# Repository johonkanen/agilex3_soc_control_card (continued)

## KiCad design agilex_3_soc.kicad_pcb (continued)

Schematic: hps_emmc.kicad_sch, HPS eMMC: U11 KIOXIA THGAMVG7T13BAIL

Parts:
C242, C244: 4u7; C_0402_1005Metric; LCSC C318563
C243: 100n; C_0201_0603Metric; LCSC C190183
C245: 220n; C_0201_0603Metric; LCSC C76932
C246: 2u2; C_0201_0603Metric; LCSC C77762
R241, R242, R243, R272, R273, R274, R275, R276, R277, R278, R279: 10k; R_0201_0603Metric; LCSC C473048
R280, R281, R282, R283, R284, R285, R286, R287, R288, R289, R290: 33R; R_0201_0603Metric; LCSC C320843
U11: THGAMVG7T13BAIL; LFBGA-153_11.5x13mm_Layout14x14_P0.5mm; LCSC C7599693

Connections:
1V8: C242.1, C243.1, R241.1, R243.1, R272.1, R273.1, R274.1, R275.1, R276.1, R277.1, R278.1, R279.1, U11.C6 (VCCQ), U11.M4 (VCCQ), U11.N4 (VCCQ), U11.P3 (VCCQ), U11.P5 (VCCQ); also elsewhere on the board
3V3: C244.1, C245.1, U11.E6 (VCC), U11.F5 (VCC), U11.J10 (VCC), U11.K9 (VCC); also elsewhere on the board
/hps_emmc/emmc_ds: R242.1, R290.2, U11.H5 (DS)
/hps_emmc/emmc_ds_hps: R290.1; also elsewhere on the board
/hps_emmc/emmc_rst_n: R243.2, U11.K5 (RST_n); also elsewhere on the board
/hps_emmc/sd_clk: R280.2, U11.M6 (CLK)
/hps_emmc/sd_clk_hps: R280.1; also elsewhere on the board
/hps_emmc/sd_cmd: R241.2, R281.2, U11.M5 (CMD)
/hps_emmc/sd_cmd_hps: R281.1; also elsewhere on the board
/hps_emmc/sd_d0: R272.2, R282.2, U11.A3 (DAT0)
/hps_emmc/sd_d0_hps: R282.1; also elsewhere on the board
/hps_emmc/sd_d1: R273.2, R283.2, U11.A4 (DAT1)
/hps_emmc/sd_d1_hps: R283.1; also elsewhere on the board
/hps_emmc/sd_d2: R274.2, R284.2, U11.A5 (DAT2)
/hps_emmc/sd_d2_hps: R284.1; also elsewhere on the board
/hps_emmc/sd_d3: R275.2, R285.2, U11.B2 (DAT3)
/hps_emmc/sd_d3_hps: R285.1; also elsewhere on the board
/hps_emmc/sd_d4: R276.2, R286.2, U11.B3 (DAT4)
/hps_emmc/sd_d4_hps: R286.1; also elsewhere on the board
/hps_emmc/sd_d5: R277.2, R287.2, U11.B4 (DAT5)
/hps_emmc/sd_d5_hps: R287.1; also elsewhere on the board
/hps_emmc/sd_d6: R278.2, R288.2, U11.B5 (DAT6)
/hps_emmc/sd_d6_hps: R288.1; also elsewhere on the board
/hps_emmc/sd_d7: R279.2, R289.2, U11.B6 (DAT7)
/hps_emmc/sd_d7_hps: R289.1; also elsewhere on the board
GND: C242.2, C243.2, C244.2, C245.2, C246.2, R242.2, U11.A6 (VSS), U11.C4 (VSSQ), U11.E7 (VSS), U11.G5 (VSS), U11.H10 (VSS), U11.J5 (VSS), U11.K8 (VSS), U11.N2 (VSSQ), U11.N5 (VSSQ), U11.P4 (VSSQ), U11.P6 (VSSQ); also elsewhere on the board
unnamed: C246.1, U11.C2 (VDDi)

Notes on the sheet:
eMMC: U11 KIOXIA THGAMVG7T13BAIL, 16 GB eMMC 5.1 (C7599693) VCCQ is 1.8 V only and must be the same 1V8 as the HPS: no level translator. CMD/DAT pull-ups 10k to 1V8 (KIOXIA: CMD 4.7-100k, DAT 10-100k). DS to HPS_IOA_16 (SDMMC_DATA_STROBE) for HS400, 10k pull-down R242. RST_n is ignored until EXT_CS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

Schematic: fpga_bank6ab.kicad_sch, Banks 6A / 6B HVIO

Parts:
U7: A5EB013B-B23B; Altera_B23B

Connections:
/fpga_bank6ab/iob6b0: U7.DD3 (6B_IO_HVIO_6B_14_TXCLK14_Data_Ctrl14); also elsewhere on the board
/fpga_bank6ab/iob6b2: U7.CV4 (6B_IO_HVIO_6B_8_TXCLK8_Data_Ctrl8); also elsewhere on the board
/fpga_bank6ab/iob6b5: U7.CH4 (6B_IO_HVIO_6B_4_TXCLK4_Data_Ctrl4); also elsewhere on the board
/fpga_bank6ab/iob6b6: U7.DN2 (6B_IO_HVIO_6B_17_TXCLK17_Data_Ctrl17); also elsewhere on the board
/fpga_bank6ab/iob6b7: U7.DM2 (6B_IO_HVIO_6B_9_PLLREFCLK1_TXCLK9_RXCLK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); also elsewhere on the board
/fpga_bank6ab/iob6b8: U7.DJ3 (6B_IO_HVIO_6B_20_TXCLK20_Data_Ctrl20); also elsewhere on the board
/fpga_bank6ab/iob6b9: U7.DH2 (6B_IO_HVIO_6B_5_TXCLK5_Data_Ctrl5); also elsewhere on the board
/fpga_bank6ab/iob6b10: U7.DH1 (6B_IO_HVIO_6B_6_TXCLK6_Data_Ctrl6); also elsewhere on the board
/fpga_bank6ab/iob6b11: U7.DF3 (6B_IO_HVIO_6B_16_TXCLK16_Data_Ctrl16); also elsewhere on the board
/fpga_bank6ab/iob6b12: U7.DE1 (6B_IO_HVIO_6B_3_TXCLK3_Data_Ctrl3); also elsewhere on the board
/fpga_bank6ab/iob6b13: U7.DC2 (6B_IO_HVIO_6B_1_TXCLK1_Data_Ctrl1); also elsewhere on the board
/fpga_bank6ab/iob6b14: U7.DC1 (6B_IO_HVIO_6B_2_TXCLK2_Data_Ctrl2); also elsewhere on the board
/fpga_led: U7.CE6 (6B_IO_HVIO_6B_18_TXCLK18_Data_Ctrl18); also elsewhere on the board

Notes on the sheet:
VCCIO_6B : 3V3

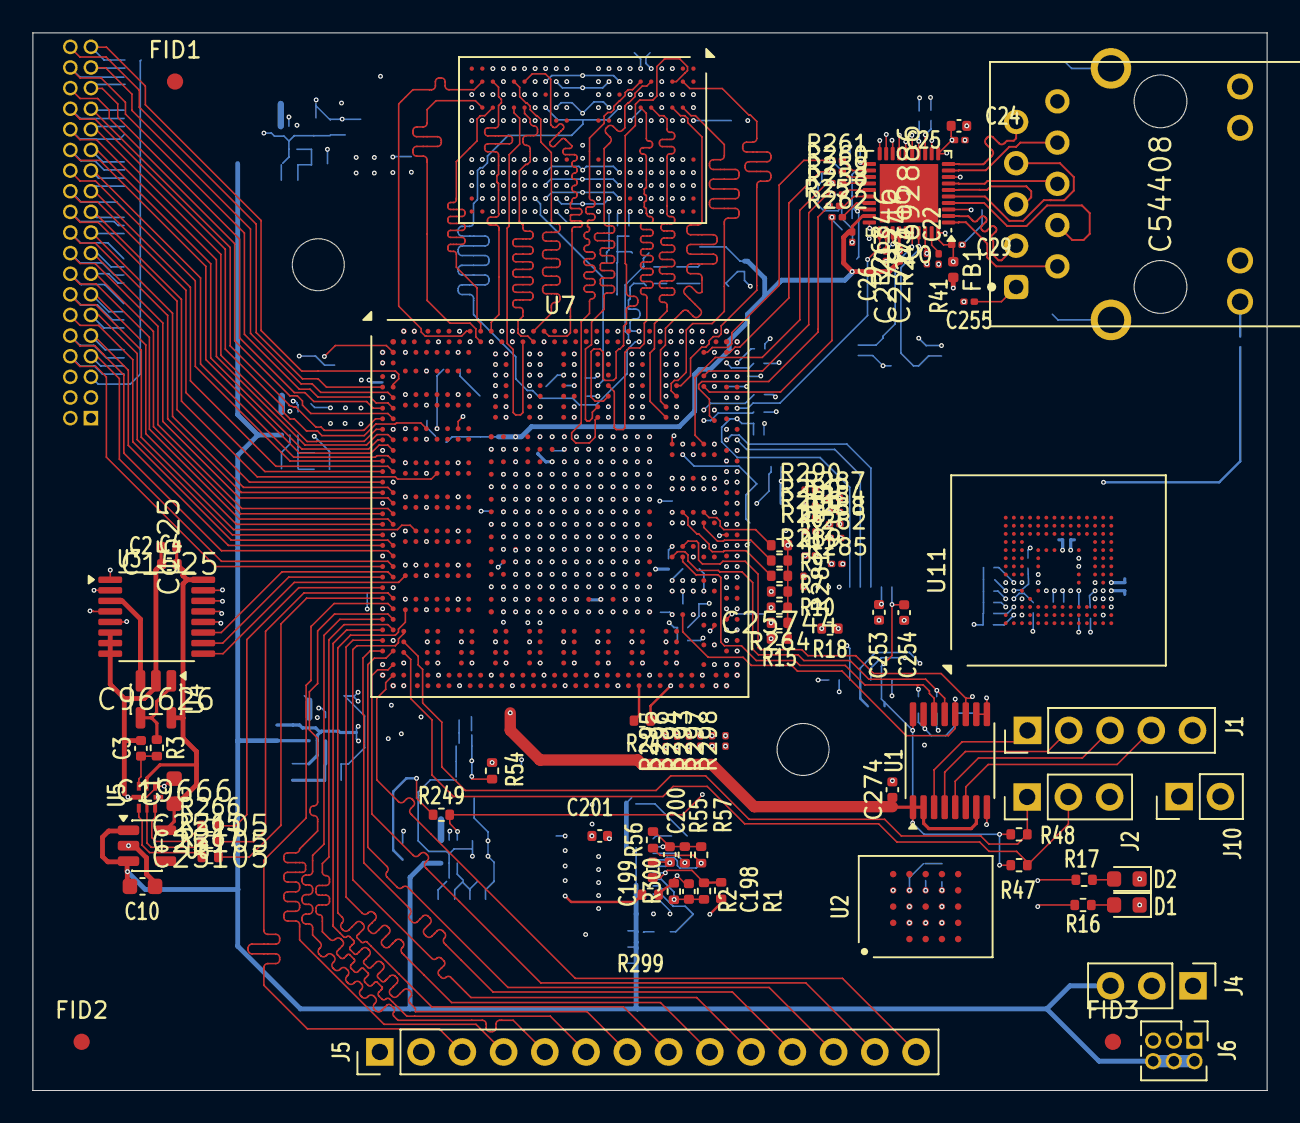
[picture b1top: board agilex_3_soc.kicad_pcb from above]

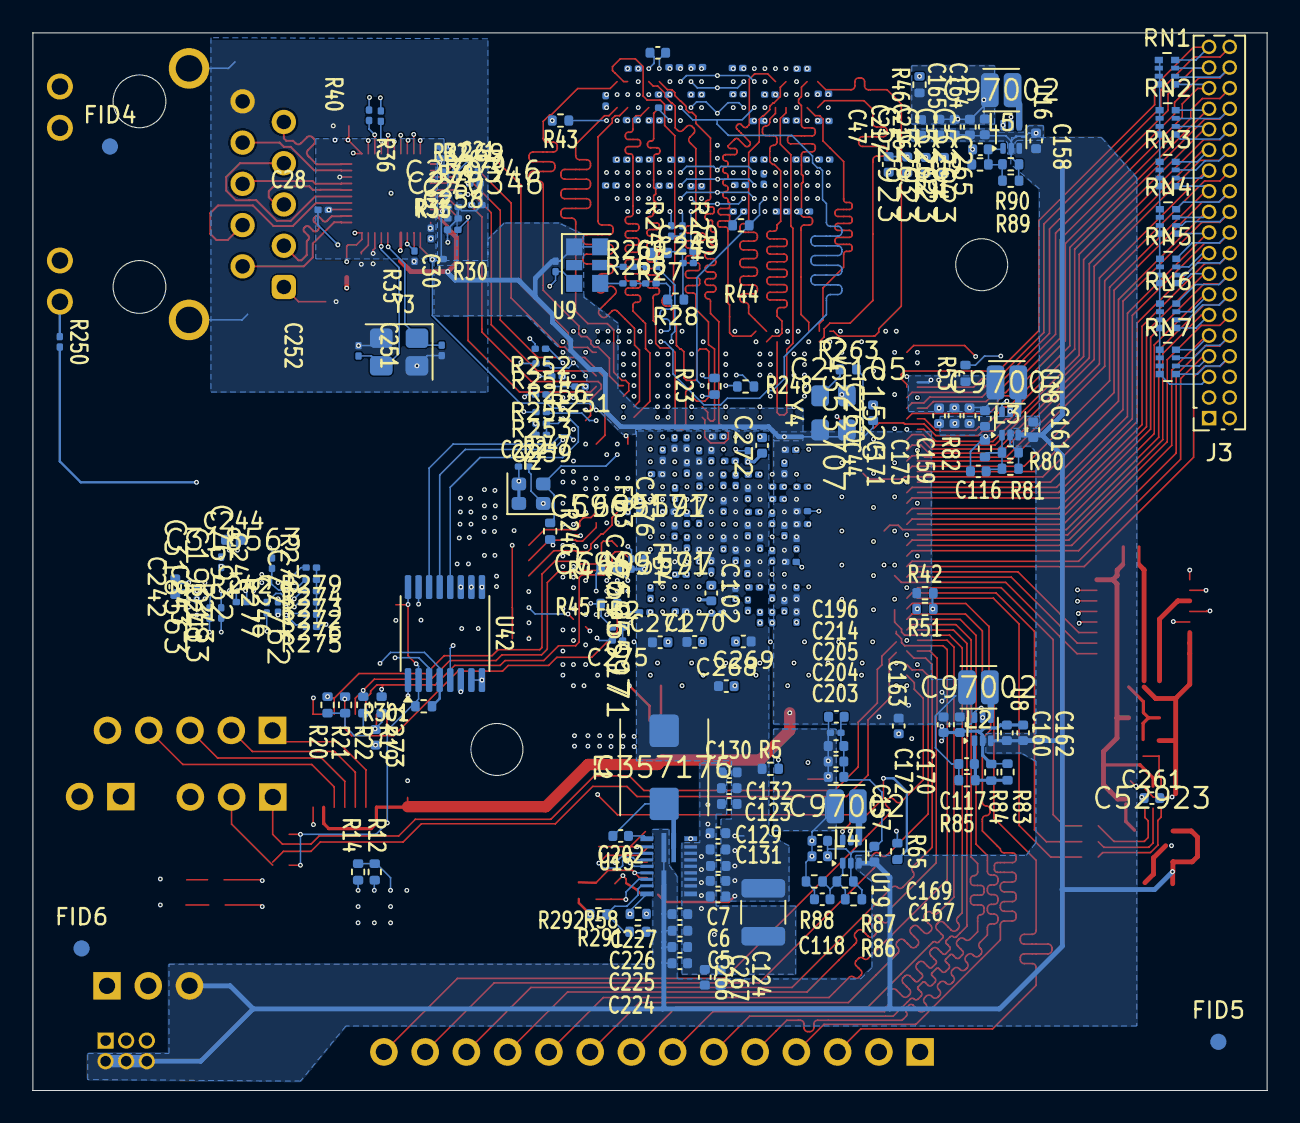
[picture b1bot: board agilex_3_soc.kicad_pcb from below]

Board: 8 copper layers, 76.0 x 65.1 mm, 363 parts (268 on the bottom side), 278 nets.

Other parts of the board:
FID1, FID2, FID3, FID4, FID5, FID6: Fiducial; Fiducial_1mm_Mask2mm
H1, H2: 960-23-33-D-AB-0 push pin; MountingHole_3.2mm_M3

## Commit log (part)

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2026-03-03 add partial libraries
2026-03-16 start sketching agilex 3 soc schematic and pcb
2026-03-17 add lpddr4 connections in schematic
2026-03-17 start making agilex 5 b23b package
2026-03-18 more balls in b23b package
2026-03-18 even more balls in b23b package
2026-03-18 place all balls in b23b pakcage
2026-03-18 latest
2026-03-19 start creating schematic symbol for agilex 5
2026-03-19 start adding schematic symbol for agilex 5
2026-03-19 start figuring out how to bulk edit schematic symbol pins
2026-03-21 add agilex 5 schematic files
2026-03-21 add .gitignore
2026-03-21 still learning how to use Git with KiCad
2026-03-21 sketch io routing between connector and agilex
2026-03-21 move adc and admux to own schematic
2026-03-22 try to figure out how to do buses
2026-03-22 start adding power supplies
2026-03-23 add ads7056 footprint
2026-03-24 start routing sd card
2026-03-24 start sketching out rgmii routes
2026-03-24 more routes
2026-03-25 even more power supply routing
2026-03-25 add correct inductor footprints for peripheral supplies
2026-03-25 clean up leftover graphics from original pcb design
2026-03-26 add vias to lppdr balls
2026-03-26 last
2026-03-29 move to 8 layers
2026-03-31 breakout 3v3 io
2026-03-31 update readme, add some comments to board
2026-03-31 add comment to lpddr routes
2026-04-04 draw a few connections
2026-04-05 start route io connectors
2026-04-07 add more io routes
2026-04-07 even more io
2026-04-07 more cleanup
2026-04-08 savegame
2026-04-08 add comments
2026-04-09 start routing power supplies
2026-04-09 add capacitors and resistors to core power
2026-04-13 sketch length matching for lpddr4
2026-04-14 test length matching lpddr4
2026-04-14 more fiddling
2026-04-14 route lpddr clock
2026-04-15 fine tune more lpddr routes
2026-04-15 add level translator for jtag
2026-04-16 add another powersupply for lpddr4
2026-04-18 add routes for power supplies
2026-04-19 savegame, after fixing wird problems with schematic sync
2026-04-19 fiddle with the jtag and uart connectors
2026-04-19 add qspi
2026-04-19 make routing sketch for qspi
2026-04-19 minor fiddling
2026-04-21 savegame before trying to fix component names
2026-04-24 fix clearance issues
2026-04-24 add plane for 1v2
2026-04-24 more fiddling with aux power supplies
2026-04-26 route ethernet rgmii io
2026-04-26 change default via size to 0.3mm
2026-04-27 change bypass caps to 0201 and start adding them to board
2026-04-27 add vcore bypass caps
2026-04-28 remove hyperram and add lpddr4 bypass caps
2026-04-28 place even more bypass caps
2026-04-29 route more rgmii io
2026-04-29 lastest
2026-05-03 add separate clock ICs instead of using programmable ic
2026-05-03 add oscillator footprint and start adding ac biasing for lpddr clock
2026-05-04 add ac biasing to lpddr ref clock
2026-05-05 move power 1v1 power supply
2026-05-06 fix some dangling routes
2026-05-07 add 1v2 flood
2026-05-09 add 5v copper to bottom layer
2026-05-09 add pcb boundary and remove original pcb
2026-05-09 fix some issues
2026-05-10 remove extra components and make 1v8 plane
2026-05-12 add sdcard level shifter
2026-05-20 increase 3v3 flood to cover nearly all 3v3 io
2026-05-20 fix some drc issues
2026-05-29 add resistors for ad channels
2026-05-31 move heat sink pins to match 960-23-33-D-AB-0 heat sink
